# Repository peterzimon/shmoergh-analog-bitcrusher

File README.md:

# Shmøergh Analog Bitcrusher

Analog bitcrusher with variable downsampling between about 100Hz and ~20kHz rate 
and wet/dry control. Note that this is a fully analog unit, no coding involved. 
KiCad version: 5.x but theoretically should work on 6.x.

Simulations are made with [CircuitJS](https://www.falstad.com/circuit/circuitjs.html) 

Find a bit more detailed circuit description on the schematics and in this 
[blogpost](https://www.peterzimon.com/analog-bitcruser).

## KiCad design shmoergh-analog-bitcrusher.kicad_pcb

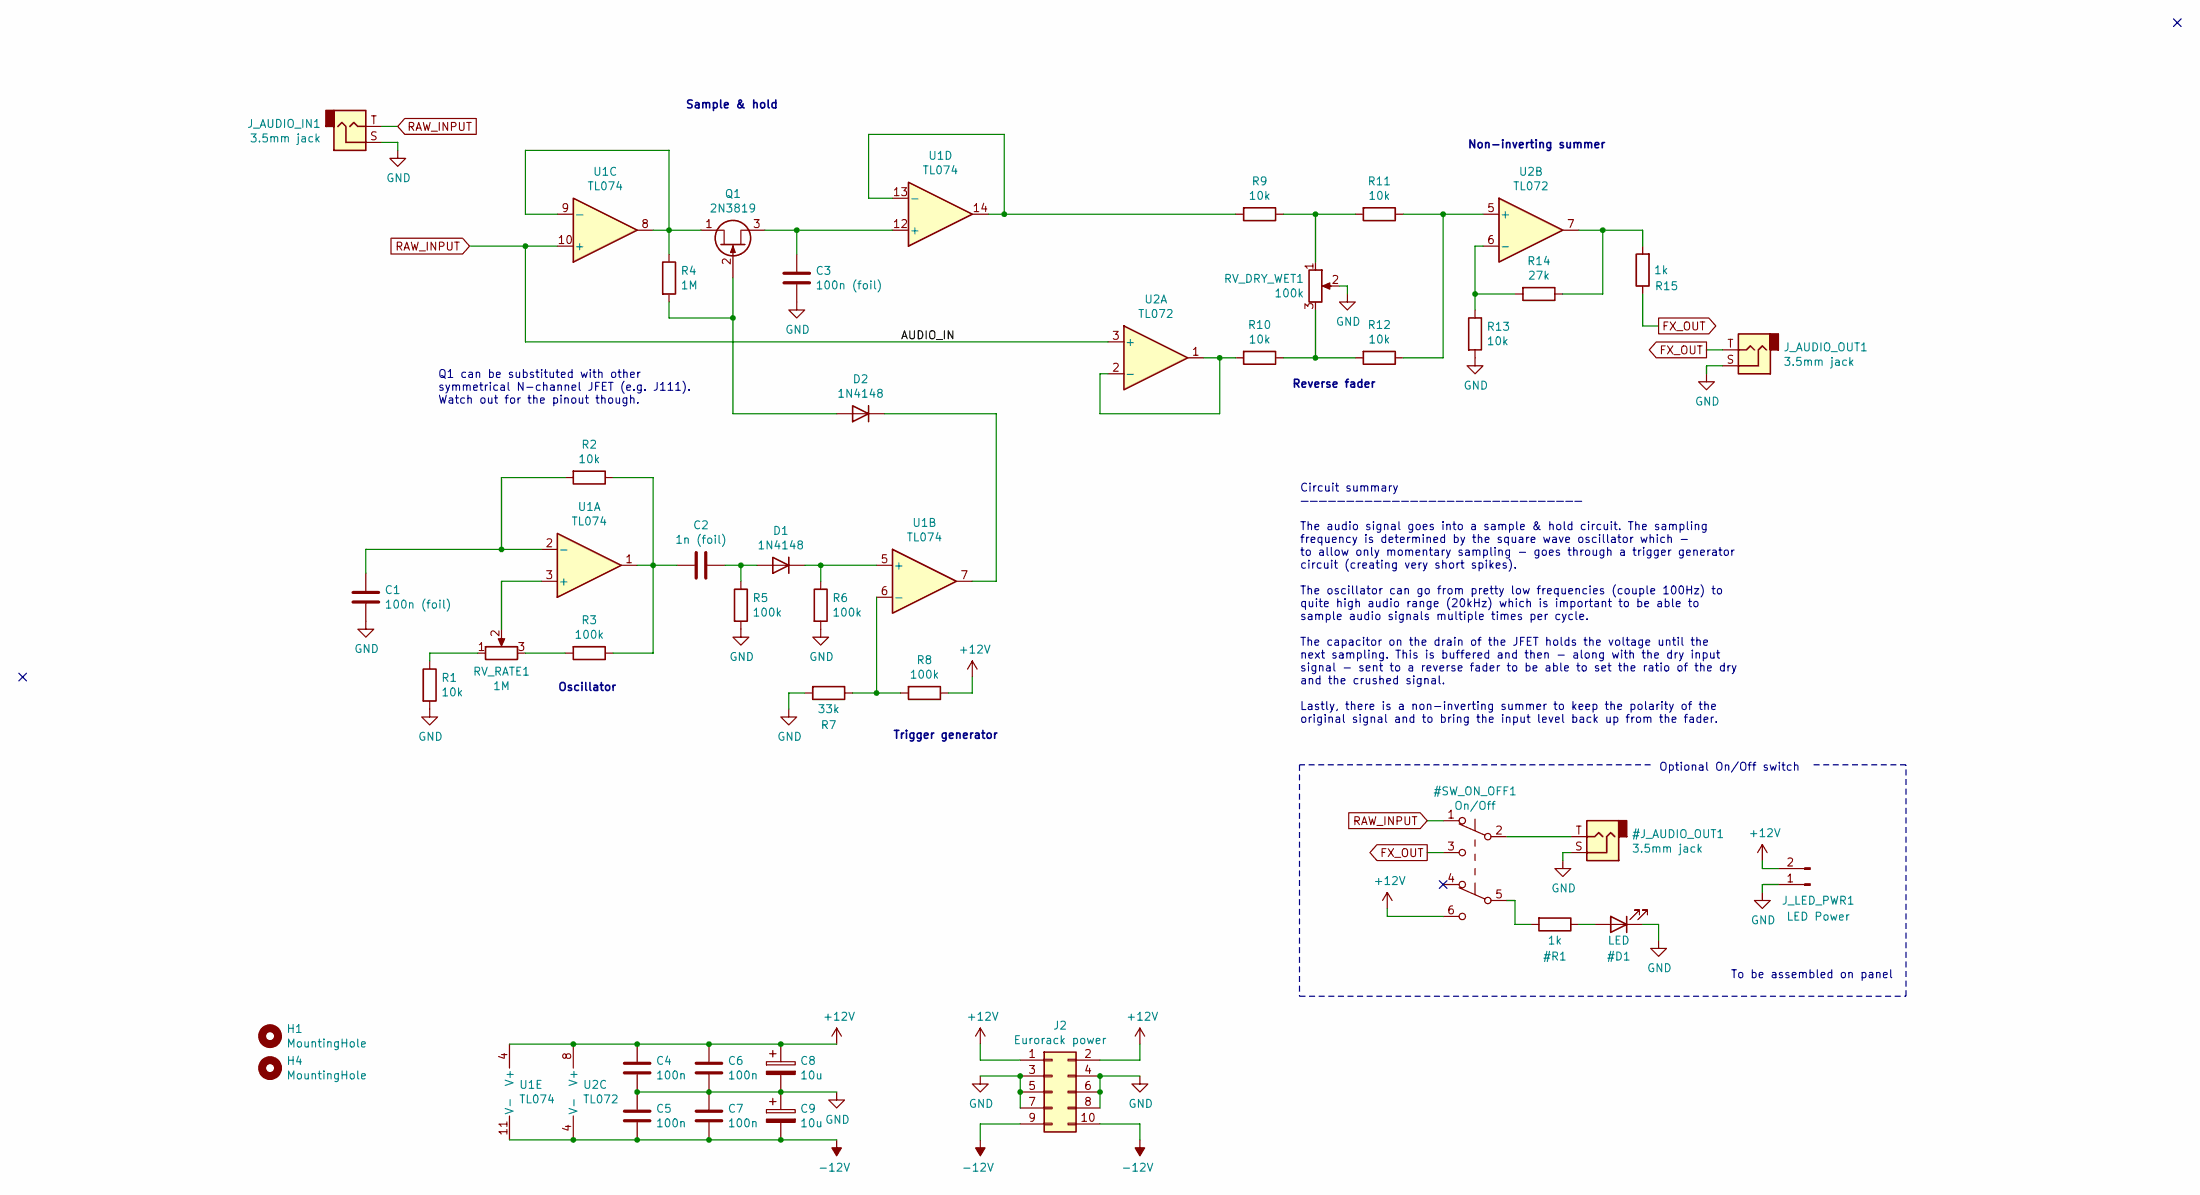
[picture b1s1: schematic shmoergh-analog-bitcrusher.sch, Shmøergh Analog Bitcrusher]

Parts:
C1, C3: 100n (foil); C_Foil_P5.48mm
C2: 1n (foil); C_Foil_P5.48mm
C4, C5, C6, C7: 100n; C_Disc_D5.0mm_W2.5mm_P2.50mm
C8, C9: 10u; CP_Radial_D5.0mm_P2.50mm
D1, D2: 1N4148; D_Axial-Vertical
H1, H4: MountingHole; MountingHole_3mm
J2: Eurorack power; Eurorack_Power_Supply
J_AUDIO_IN1: 3.5mm jack; NSL25_01x02_Vertical-AudioJack-TS
J_AUDIO_OUT1: 3.5mm jack; NSL25_01x02_Vertical-AudioJack-TS
J_LED_PWR1: LED Power; NSL25_01x02_Vertical
Q1: 2N3819; TO-92_Inline
R1, R2, R9, R10, R11, R12, R13: 10k; R_Axial_Vertical
R3, R5, R6, R8: 100k; R_Axial_Vertical
R4: 1M; R_Axial_Vertical
R7: 33k; R_Axial_Vertical
R14: 27k; R_Axial_Vertical
R15: 1k; R_Axial_Vertical
RV_DRY_WET1: 100k; NSL25_01x03_Vertical
RV_RATE1: 1M; NSL25_01x03_Vertical
U1: TL074; DIP-14_W7.62mm
U2: TL072; DIP-8_W7.62mm

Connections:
-12V: C5.2, C7.2, C9.2, J2.9, J2.10, U1.11 (V-), U2.4 (V-)
unnamed: C1.1, R2.2, U1.2 (-)
unnamed: C2.1, D1.2 (A), R5.1
unnamed: C2.2, R2.1, R3.1, U1.1
unnamed: C3.1, Q1.3 (S), U1.12 (+)
unnamed: D1.1 (K), R6.1, U1.5 (+)
unnamed: D2.1 (K), U1.7
unnamed: D2.2 (A), Q1.2 (G), R4.2
unnamed: Q1.1 (D), R4.1, U1.8, U1.9 (-)
unnamed: R1.1, RV_RATE1.1
unnamed: R3.2, RV_RATE1.3
unnamed: R7.1, R8.2, U1.6 (-)
unnamed: R9.2, U1.13 (-), U1.14
unnamed: R10.1, R12.2, RV_DRY_WET1.3
unnamed: R10.2, U2.1, U2.2 (-)
unnamed: R11.1, R12.1, U2.5 (+)
unnamed: R9.1, R11.2, RV_DRY_WET1.1
unnamed: R13.1, R14.2, U2.6 (-)
unnamed: R14.1, R15.2, U2.7
unnamed: RV_RATE1.2, U1.3 (+)

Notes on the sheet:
Oscillator
Trigger generator
Reverse fader
Sample & hold
Non-inverting summer
Q1 can be substituted with other symmetrical N-channel JFET (e.g. J111). Watch out for the pinout though.
Circuit summary ——————————————————————————————— The audio signal goes into a sample & hold circuit. The sampling frequency is determined by the square wave oscillator which - to allow only momentary sampling - goes through a trigger generator circuit (creating very short spikes). The oscillator can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
Optional On/Off switch
To be assembled on panel

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
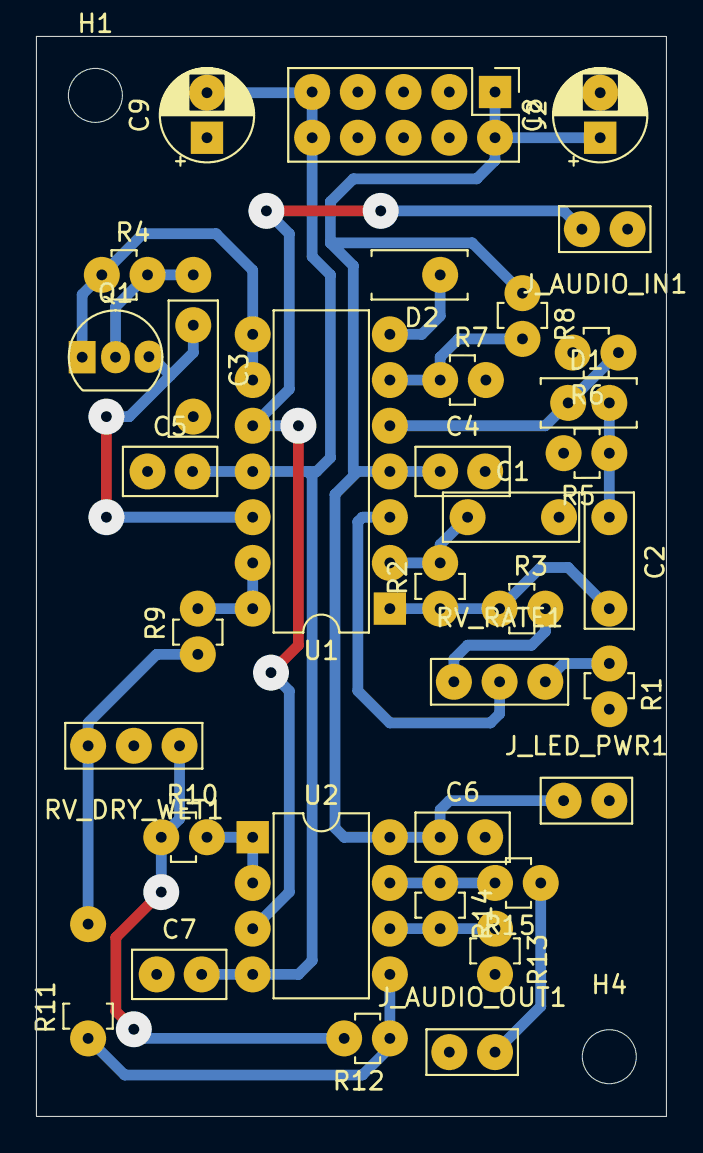
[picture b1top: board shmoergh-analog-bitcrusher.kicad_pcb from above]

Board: 2 copper layers, 35.0 x 60.0 mm, 37 parts (0 on the bottom side), 24 nets.

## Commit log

2022-06-25 Added bitcrusher circuit
2022-06-25 Updated plots
2022-06-27 Added on/off switch to schematics
2022-07-01 Added readme
